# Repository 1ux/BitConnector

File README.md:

*„Jede Lösung eines Problems ist ein neues Problem.“ - J. W. Goehte*

# BitConnector

The BitConnector is a Complex Programmable Logic Device (CPLD) Board, optimized for hardware-based, digital prototype design on a breadboard.
The BitConnector is designed to represent a classic DIP chip in 2.54mm pitch with 2 * 20 pins. 
Configurations that are present in an HDL/schematic are transmitted via JTAG and stored permanently on the CPLD.

<table><tr>
<td>    </td>
<td>    </td>
<td>    </td>
<td>    </td>
</tr></table>

## Usage & Documentation

Like every IC the BitConnector needs a clean operating voltage without ripple.
In practice, the following methods have proven successful:

- Protect the 3V3 Pin with 100nf and 10nf capacitors against GND.
- Keep the 3V3 and GND connections short and stable.
- Avoid long signal and test leads (up to 25 cm) to the inputs during operation.
- If you are having trouble getting a clean clock input, set „implementation template“ to „optimize density“ in Process Properties/Fitting
  or disable the special globally routed nets as described [here](https://web.archive.org/web/20210309172427/https://www.xilinx.com/support/documentation/sw_manuals/help/iseguide/mergedProjects/destech/html/cd_using_global_nets.htm)

Example experimental setup:

- there is a detailed German board [documentation](doc/Board_Doc_German.pdf) :de:
- here is the preview for the [schematic](doc/schematic_v5Xe.pdf)
- files for board production have also been published in [Gerber](gerbers/gerbers_v5Xe.zip) format
- for a revision overview check: [changelog](changelog.txt)
- for all other questions, study the Kicad project.

|    |          |           |            |          |                   |
| :- | :------: | :-------- | :--------: | :------: | :---------------- |
| **DIP-left**  | **CPLD-Pin** | **function**   | **DIP-right**  | **CPLD-Pin** | **function** |
| 1  |    1     |GPIO, GCK3|      1      |  15,35   | 3V3/V<sub>ccINT</sub> |
| 2  |    2     | GPIO     |      2      |    26    | VCC V<sub>ccIO</sub>  |
| 3  |    3     | GPIO     |      3      |    44    | GPIO, GCK2            |
| 4  |    5     | GPIO     |      4      |    43    | GPIO, GCK1            |
| 5  |    6     | GPIO     |      5      |    42    | GPIO                  |
| 6  |    7     | GPIO     |      6      |    41    | GPIO                  |
| 7  |    8     | GPIO     |      7      |    40    | GPIO                  |
| 8  |    12    | GPIO     |      8      |    39    | GPIO                  |
| 9  |    13    | GPIO     |      9      |    38    | GPIO                  |
| 10 |    14    | GPIO     |      10     |    37    | GPIO                  |
| 11 |    16    | GPIO     |      11     |    36    | GPIO, GTS1            |
| 12 |    18    | GPIO     |      12     |    34    | GPIO, GTS2            |
| 13 |    19    | GPIO     |      13     |    32    | GPIO                  |
| 14 |    20    | GPIO     |      14     |    31    | GPIO                  |
| 15 |    21    | GPIO     |      15     |    30    | GPIO                  |
| 16 |    22    | GPIO     |      16     |    29    | GPIO                  |
| 17 |    23    | GPIO     |      17     |    28    | GPIO                  |
| 18 |    11    | TCK      |      18     |    27    | GPIO                  |
| 19 |    24    | TDO      |      19     |    9     | TDI                   |
| 20 |  17,25,4 | GND      |      20     |    10    | TMS                   |                                                      |

Supplements and notes:

- **GPIO**=General Purpose In/Output, **GRS**=Global Reset, **GTS**=Global Tri-State, **GCK**=Global Clock, **TDI**=Test Data In, **TDO**=Test Data Out, **TCK**=Test Clk, **TMS**=Test Mode Select, V<sub>ccINT</sub>=Supply voltage internal logic, V<sub>ccIO</sub>=Supply voltage output driver
- Pin 33 is connected to the onboard push-button with GRS.
- With hardware debouncing, the push-button is high-active, otherwise it is low-active.

## Build

|       |                               |               |               |               |
| :-    | :---------------------------: | :--------:    | :---------:   |   :---------: |
|   No  |   component                   |  value        |   quantity    |   package     |
|   1   |   Unpolarized capacitor       |   100nF       |   3           |   0603        |
|   2   |   Unpolarized capacitor       |   10nF        |   3           |   0603        |
|  (3)  |   Unpolarized capacitor       |   100nF       |   1           |   0603        |
|  (4)  |   Resistor                    |   100K        |   1           |   0805        |
|  (5)  |   Resistor                    |   10K         |   1           |   0805        |
|   6   |   Resistor                    |   10K         |   4           |   0805        |
|   7   |   Resistor                    |   120         |   1           |   0805        |
|   8   |   LED                         |   blue        |   1           |   1206        |
|   9   |   Push button                 |   6 mm        |   1           |   THT         |
|   10  |   Pin Header 1x20             |   2.54 mm     |   2           |   vertical    |
|   11  |   IDC Header 2x3              |   2.54 mm     |   1           |   vertical    |
|  (12) |   Pin Socket 1x2              |   2.54 mm     |   1           |   vertical    |
|  (13) |   74LVC2G14                   |   Schmitt-Tr  |   1           |   SOT457      |
|   14  |   XC9536XL/XC9572XL           |   CPLD        |   1           |   VQ44/VQG44  |

- The components without brackets correspond to the minimum configuration (without hardware debouncing).
- You can use the [XC9536XL](https://www.xilinx.com/support/documentation/data_sheets/ds058.pdf) or the more powerful [XC9572XL](https://www.xilinx.com/support/documentation/data_sheets/ds057.pdf) CPLD.
- The BitConverter was designed in a minimal configuration with commercially available components.
- The bracketed components are optional for hardware debouncing/Schmitt trigger action via [74LVC2G14](https://assets.nexperia.com/documents/data-sheet/74LVC2G14.pdf).
- If you make the board without hardware debouncing, please set the solderjumper J1.
- In addition to the schematic, the [Gerber](https://github.com/1ux/BitConnector/raw/master/gerbers/gerbers_v5X.zip) files for board production have also been published.

## Thanks to:

- Jeremy Heighway for mentoring English grammar and spelling.
- [Jana Weigel](https://janaweigel.wordpress.com/) for graphic design consulting, mentoring German grammar and spelling.
- [Lothar Miller](http://www.lothar-miller.de/) for PCB design consulting.
- [mikrocontroller.net](https://www.mikrocontroller.net/topic/492067) for failure analysis and life experience ;).

## Licence
This project by Michael Krause is distributed in the hope that it will be useful, but WITHOUT ANY WARRANTY.

This project is free: you can redistribute it and/or modify
it under the terms of [CC BY-SA 4.0](https://creativecommons.org/licenses/by-sa/4.0/deed.de)
Excluded from this licence is the logo(./doc/Figures/Logo.pdf).
Should you change or delete something, please remove the logo.

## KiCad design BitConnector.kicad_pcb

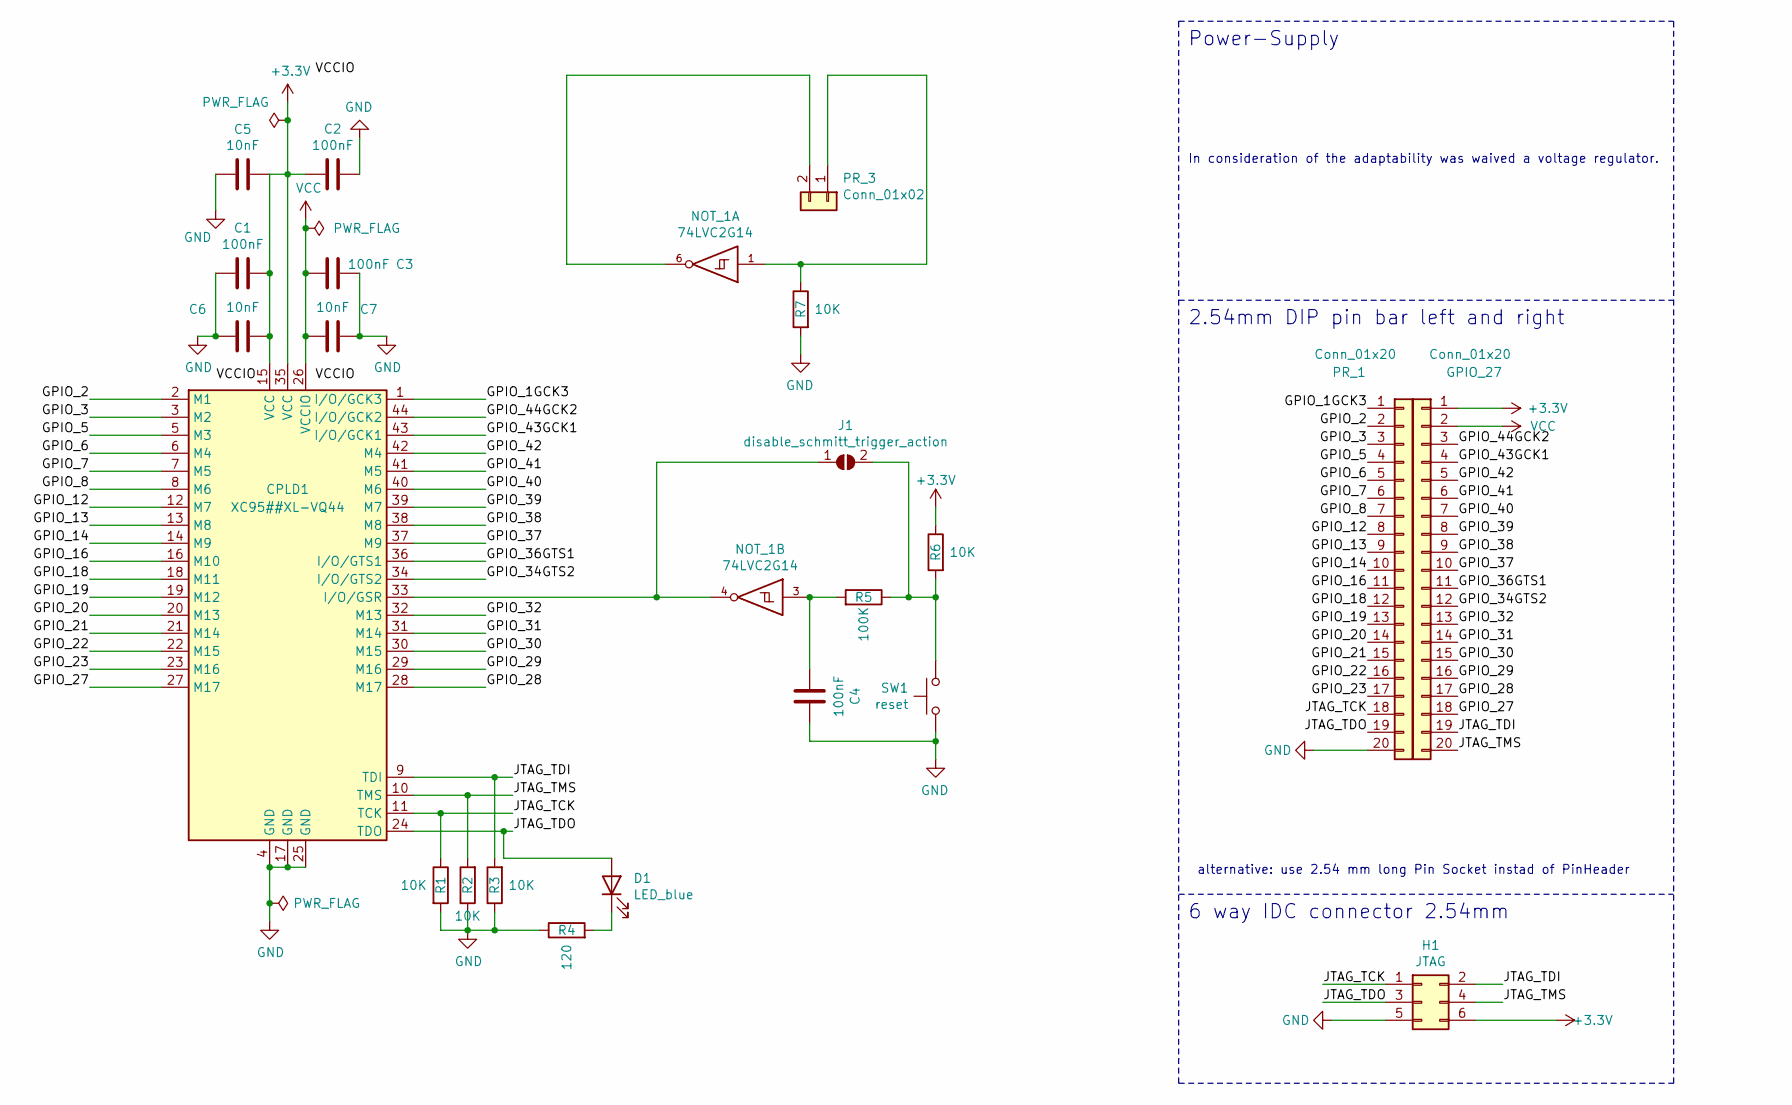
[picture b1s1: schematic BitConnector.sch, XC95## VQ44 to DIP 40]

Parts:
C1, C2, C3, C4: 100nF; C_0603_1608Metric
C5, C6, C7: 10nF; C_0603_1608Metric
CPLD1: XC95##XL-VQ44; LQFP-44_10x10mm_P0.8mm
D1: LED_blue; LED_1206_3216Metric_Castellated
GPIO_27: Conn_01x20; PinHeader_1x20_P2.54mm_Vertical
H1: JTAG; IDC-Header_2x03_P2.54mm_Vertical
J1: disable_schmitt_trigger_action; SolderJumper-2_P1.3mm_Open_RoundedPad1.0x1.5mm
NOT_1: 74LVC2G14; SC-74-6_1.5x2.9mm_P0.95mm
PR_1: Conn_01x20; PinHeader_1x20_P2.54mm_Vertical
PR_3: Conn_01x02; PinSocket_1x02_P2.54mm_Vertical
R1, R2, R3, R6, R7: 10K; R_0805_2012Metric_Pad1.20x1.40mm_HandSolder
R4: 120; R_0805_2012Metric_Pad1.20x1.40mm_HandSolder
R5: 100K; R_0805_2012Metric_Pad1.20x1.40mm_HandSolder
SW1: reset; SW_PUSH_6mm

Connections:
+3V3: C1.1, C2.2, C5.1, C6.1, CPLD1.15 (VCC), CPLD1.35 (VCC), GPIO_27.1, H1.6, R6.1
/GPIO_1GCK3: CPLD1.1 (I/O/GCK3), PR_1.1
/GPIO_2: CPLD1.2 (M1), PR_1.2
/GPIO_3: CPLD1.3 (M2), PR_1.3
/GPIO_5: CPLD1.5 (M3), PR_1.4
/GPIO_6: CPLD1.6 (M4), PR_1.5
/GPIO_7: CPLD1.7 (M5), PR_1.6
/GPIO_8: CPLD1.8 (M6), PR_1.7
/GPIO_12: CPLD1.12 (M7), PR_1.8
/GPIO_13: CPLD1.13 (M8), PR_1.9
/GPIO_14: CPLD1.14 (M9), PR_1.10
/GPIO_16: CPLD1.16 (M10), PR_1.11
/GPIO_18: CPLD1.18 (M11), PR_1.12
/GPIO_19: CPLD1.19 (M12), PR_1.13
/GPIO_20: CPLD1.20 (M13), PR_1.14
/GPIO_21: CPLD1.21 (M14), PR_1.15
/GPIO_22: CPLD1.22 (M15), PR_1.16
/GPIO_23: CPLD1.23 (M16), PR_1.17
/GPIO_27: CPLD1.27 (M17), GPIO_27.18
/GPIO_28: CPLD1.28 (M17), GPIO_27.17
/GPIO_29: CPLD1.29 (M16), GPIO_27.16
/GPIO_30: CPLD1.30 (M15), GPIO_27.15
/GPIO_31: CPLD1.31 (M14), GPIO_27.14
/GPIO_32: CPLD1.32 (M13), GPIO_27.13
/GPIO_34GTS2: CPLD1.34 (I/O/GTS2), GPIO_27.12
/GPIO_36GTS1: CPLD1.36 (I/O/GTS1), GPIO_27.11
/GPIO_37: CPLD1.37 (M9), GPIO_27.10
/GPIO_38: CPLD1.38 (M8), GPIO_27.9
/GPIO_39: CPLD1.39 (M7), GPIO_27.8
/GPIO_40: CPLD1.40 (M6), GPIO_27.7
/GPIO_41: CPLD1.41 (M5), GPIO_27.6
/GPIO_42: CPLD1.42 (M4), GPIO_27.5
/GPIO_43GCK1: CPLD1.43 (I/O/GCK1), GPIO_27.4
/GPIO_44GCK2: CPLD1.44 (I/O/GCK2), GPIO_27.3
/JTAG_TCK: CPLD1.11 (TCK), H1.1, PR_1.18, R1.1
/JTAG_TDI: CPLD1.9 (TDI), GPIO_27.19, H1.2, R3.2
/JTAG_TDO: CPLD1.24 (TDO), D1.2 (A), H1.3, PR_1.19
/JTAG_TMS: CPLD1.10 (TMS), GPIO_27.20, H1.4, R2.2
GND: C1.2, C2.1, C3.1, C4.2, C5.2, C6.2, C7.1, CPLD1.4 (GND), CPLD1.17 (GND), CPLD1.25 (GND), H1.5, PR_1.20, R1.2, R2.1, R3.1, R4.1, R7.2, SW1.2; also elsewhere on the board
unnamed 39: C4.1, NOT_1.3, R5.2; also elsewhere on the board
unnamed 40: CPLD1.33 (I/O/GSR), J1.1 (A), NOT_1.4; also elsewhere on the board
unnamed: D1.1 (K), R4.2
unnamed: J1.2 (B), R5.1, R6.2, SW1.1
unnamed 43: NOT_1.1, PR_3.1, R7.1; also elsewhere on the board
unnamed 44: NOT_1.6, PR_3.2; also elsewhere on the board
VCC: C3.2, C7.2, CPLD1.26 (VCCIO), GPIO_27.2; also elsewhere on the board

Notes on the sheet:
6 way IDC connector 2.54mm
2.54mm DIP pin bar left and right
Power-Supply
alternative: use 2.54 mm long Pin Socket instad of PinHeader
In consideration of the adaptability was waived a voltage regulator.

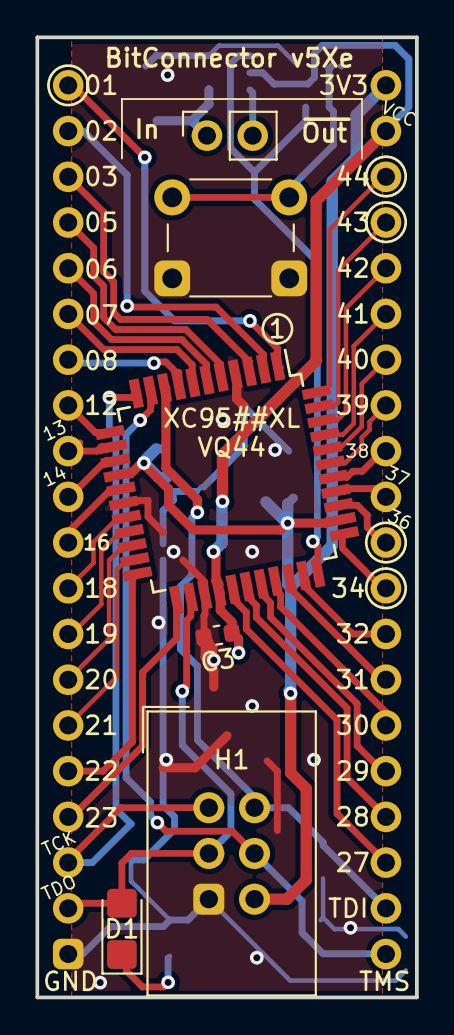
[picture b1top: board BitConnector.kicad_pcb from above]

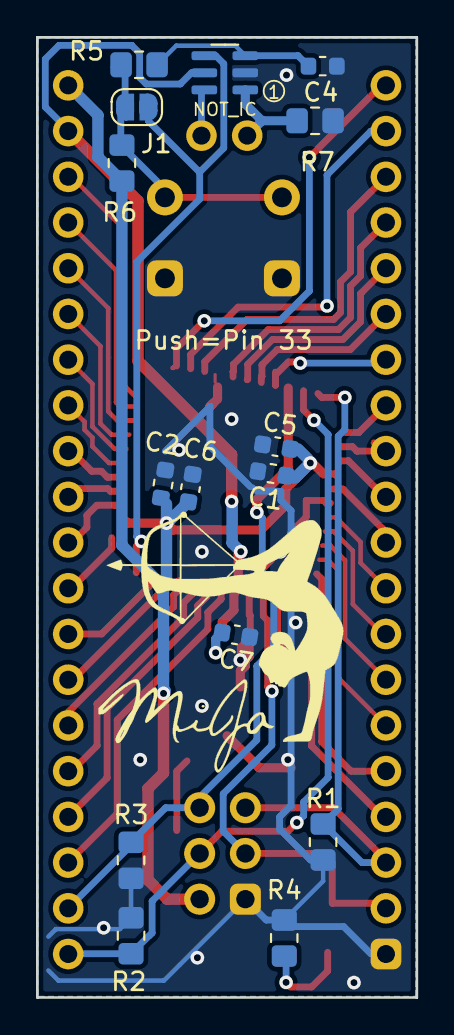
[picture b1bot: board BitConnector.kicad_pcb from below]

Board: 2 copper layers, 21.1 x 53.3 mm, 23 parts (17 on the bottom side), 46 nets.

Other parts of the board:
NOT_IC: 74LVC2G14; SC-74-6_1.5x2.9mm_P0.95mm

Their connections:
GND: NOT_IC.2; also elsewhere on the board
unnamed 39: NOT_IC.3; also elsewhere on the board
unnamed 40: NOT_IC.4; also elsewhere on the board
unnamed 43: NOT_IC.1; also elsewhere on the board
unnamed 44: NOT_IC.6; also elsewhere on the board
VCC: NOT_IC.5; also elsewhere on the board

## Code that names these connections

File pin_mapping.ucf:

#---------------------------------------
#CPLD-DIP-Board ucf pin definitions file |
#---------------------------------------
#If you do not know what you are doing	|
#use max 3.3V for any cpld pin.			|
#---------------------------------------
#by Michael Krause

#left DIP-side

#NET	GPIO_1GCK3		LOC="1";
#NET	GPIO_2			LOC="2";
#NET	GPIO_3			LOC="3";
#NET	GPIO_5			LOC="5";
#NET	GPIO_6        		LOC="6";
#NET	GPIO_7			LOC="7";
#NET  	GPIO_8			LOC="8";
#NET  	GPIO_12			LOC="12";
#NET  	GPIO_13        		LOC="13";
#NET  	GPIO_14			LOC="14";
#NET  	GPIO_16			LOC="16";
#NET  	GPIO_18			LOC="18";
#NET  	GPIO_19        		LOC="19";
#NET  	GPIO_20			LOC="20";
#NET  	GPIO_21			LOC="21";
#NET  	GPIO_22			LOC="22";
#NET  	GPIO_23			LOC="23";
#NET  	TCK			LOC="11";
#NET  	TDO			LOC="24";

#right DIP-side
#NET  	GPIO_44GCK2		LOC="44";
#NET  	GPIO_43GCK1        	LOC="43";
#NET  	GPIO_42			LOC="42";
#NET  	GPIO_41			LOC="41";
#NET  	GPIO_40        		LOC="40";
#NET  	GPIO_39			LOC="39";
#NET  	GPIO_38			LOC="38";
#NET  	GPIO_37			LOC="37";
#NET  	GPIO_36GTS1        	LOC="36";
#NET  	GPIO_34GTS2		LOC="34";
#NET  	GPIO_32			LOC="32";
#NET  	GPIO_31			LOC="31";
#NET  	GPIO_30        		LOC="30";
#NET  	GPIO_29			LOC="29";
#NET	GPIO_28			LOC="28";
#NET	GPIO_27			LOC="27";
#NET  	TDI			LOC="9";
#NET  	TMS			LOC="10";

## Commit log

2019-10-12 Initialer Commit
2019-10-12 add readme
2019-10-12 add pic in readme
2019-10-12 fix pic in readme
2019-10-12 edit README - add BOM - add pin overview - edit some graphics
2019-10-12 paste graphics side by side
2019-10-21 Update und expand descriptions in the readme
2019-10-28 introduce changelog
2019-11-07 Add gitignore
2019-11-07 Introduce BitConnector_v4X - Add hardware debouncing via schmitt trigger action - The Schmnitt Triger adds another external inverter. Usable over J2. - As an alternative, add jumper to bridge the Sch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
2019-11-07 Adapt the README to the new version of v4X.
2019-11-08 Revised changelog for version v4X!
2019-11-08 Correct specification in the BOM for caps
2019-11-11 Consider the latex files in gitignore
2019-11-11 Add doc, add chapters on voltage characteristics.
2019-11-11 Fix spelling mistakes in doc
2019-11-12 Introduce graphics to v4X
2019-11-13 Expanded image documentation in README
2019-11-26 Consider Mr Heighway Grammar suggestions.
    Insert a thank you section.
2019-11-26 Customize the description of the new v4X version.
2019-11-26 Change name of the doc to allow permanent links.
2019-11-26 Add more hyperlinks and add quote.
2019-11-26 Correct the package format information
    add hyperlinks to CPLD datasheets
2019-11-26 Change package for 74LVC2G14 from SOT363 to SOT457
2019-11-26 Begin to adapt the description and doc to v4X.
    - Adapt graphics in doc to the new v4x version.
    - Begin the description of hadware debouncing.
2019-12-18 insert merge request from mr heighway for README
2021-02-05 first attempt of the new v5X version
    details:
    - switch solder pad for resistors from 1.15mm to 1.20mm
    - add additional 10nF bypass capacitor according to
    Xilinx XAPP104 (3.0.1) specification
    - Completely new board layout created to improve
    GND and Vcc connection and suppress interference signals
2021-02-05 Resize previev picture of the BitConnector 5
2021-02-05 Revise board layout
    according to suggestions for improvement, see under:
    https://www.mikrocontroller.net/topic/492067
    thx Lothar
2021-02-07 Adjust README and graphics to the new version 5
2021-02-11 revised/updated hyperlinks
2021-02-13 Set more hyperlinks from for better documentation!
2021-03-08 Update issue templates
2021-03-21 Complete the assembly list.
2021-04-14 Revised and advanced chapters on JTAG
2021-04-14 Add hints to GND problems in the gck pins
2021-04-14 Specify GND issues on the GCK globally routed nets
2021-04-25 Test circuit with improved GND connection connection
2021-05-24 Optimize the distance between the two pin headers
2021-06-04 Expand chapter 7 on cable manufacturing
2021-06-04 add best practice for the operation of BitConnector
2021-06-04 Changes in chapter 7
2021-06-24 Revise the concept of PCB labeling
2021-06-24 change html links to project to relative links
2021-06-24 Change pin designation in schematic and
    - expand debouncing chapter
2021-06-24 Revised key data overview according new pin scheme
2021-06-25 add new graphics to current vers.& delete old ones
2021-06-25 add missing file extension
2021-06-25 Map new PCB label to table
2021-06-28 update test environment
2021-07-07 Revise and expand chapter 4 about Vcc
2021-07-07 Passe die Pinzuweisung an die v5Xe Version an.
    The designation of the pins now matches the circuit diagram.
2021-07-08 correct output characteristic & revise chapter 4.3
2021-09-04 update Xilinx source for GCK disabling

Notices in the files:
BitConnector.kicad_pcb:
License: CC BY-SA 5.0
BitConnector.sch:
License: CC BY-SA 4.0
